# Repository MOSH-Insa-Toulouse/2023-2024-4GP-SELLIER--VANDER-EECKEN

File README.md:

<h1 align="center">📈 Projet capteur graphène 📉</h1>
<h2 align="center">👨‍🔬 Par VANDER-EECKEN Néo et SELLIÉ Pierre 👨‍🔬</h2>
<h3 align="center">🏫 Pour l'INSA de Toulouse, département du Génie Physique, année 2023 - 2024 🎓</h3>

<p align="center">
  
</p>

<h1 align="center">🔩 Mesure de contrainte avec capteur graphène sous Arduino 🤖</h1>

## 📝 Description

Ce projet introduit une approche novatrice pour la mesure de contrainte en exploitant les propriétés uniques du graphène à travers un capteur dédié, envisagé comme une alternative prometteuse aux jauges de contrainte conventionnelles. Grâce à l'emploi du graphène, connu pour sa sensibilité et sa flexibilité, ce capteur offre un potentiel intéressant pour une variété d'applications de mesure. Le système est bâti autour d'une plateforme Arduino, facilitant ainsi son accessibilité et sa manipulation pour tous.

Le projet inclut un circuit d'amplification pour le signal du capteur en graphène, assurant une précision accrue des mesures. Un potentiomètre digital permet d'ajuster le gain de ce circuit, offrant ainsi une calibration précise selon les besoins spécifiques de l'application. Cette approche est complétée par des modules tels que le Bluetooth, un écran OLED et un encodeur rotatoire, qui enrichissent l'expérience utilisateur et la fonctionnalité du système.

En complément de la programmation Arduino, ce projet est accompagné de fichiers KiCad détaillant le design d'un Shield UNO personnalisé. Cette approche modulaire facilite le montage et l'intégration de l'ensemble des composants, permettant ainsi une grande flexibilité dans la configuration du système.

## 🌟 Fonctionnalités

- **Capteur de contrainte en graphène** : Exploite les propriétés du graphène pour une mesure de contrainte.
- **Circuit d'amplification avec réglage** : Potentiomètre digital pour ajuster le gain.
- **Modules intégrés** : Communication Bluetooth, affichage sur écran OLED et interaction utilisateur via encodeur rotatoire.
- **Design modulaire** : Fichiers KiCad pour un Shield UNO personnalisé.

Pour plus d'informations, vous pouvez retrouver la datasheet du produit [ici](https://github.com/MOSH-Insa-Toulouse/2023-2024-4GP-SELLIER--VANDER-EECKEN/blob/main/Datasheet.pdf).

## 📦 Matériel nécessaire

- Capteur graphène (à fabriquer soi-même)
- Arduino UNO (https://store.arduino.cc/products/arduino-uno-rev3)
- Circuit d'amplification : LTC1050#CN8 + 2x100kΩ ; 10kΩ ; 1kΩ ; 3x100nF ; 1µF (https://www.analog.com/en/products/ltc1050.html)
- Potentiomètre digital : MCP41050-IP (https://www.microchip.com/en-us/product/mcp41050)
- Module Bluetooth : HC-05 (https://www.gotronic.fr/art-module-bluetooth-hc05-26097.htm)
- Écran OLED : SSD1306 (https://electropeak.com/0-96-oled-64x128-display-module)
- Encodeur rotatoire (https://www.az-delivery.de/fr/products/drehimpulsgeber-modul)
- Capteur FLEX (https://www.kiwi-electronics.com/en/short-flex-bend-sensor-2172)

## 🔧 Installation

1. Assemblez le circuit selon les schémas fournis dans les fichiers KiCad.
2. Connectez les modules et le capteur en suivant le schéma KiCad.
3. Installez l'IDE Arduino et installez la librairie "U8glib"
4. Téléchargez le code source sur votre Arduino UNO.

## 🖥️ Utilisation

Utilisez l'encodeur rotatoire pour naviguer dans le menu de l'écran OLED.

## 🤝 Contribuer

Les contributions sont bienvenues ! Si vous avez des idées d'amélioration, n'hésitez pas à forker le projet, soumettre des pull requests ou ouvrir des issues.

## 📜 Licence

Distribué sous la GNU General Public License (GPL), favorisant un écosystème ouvert et collaboratif.

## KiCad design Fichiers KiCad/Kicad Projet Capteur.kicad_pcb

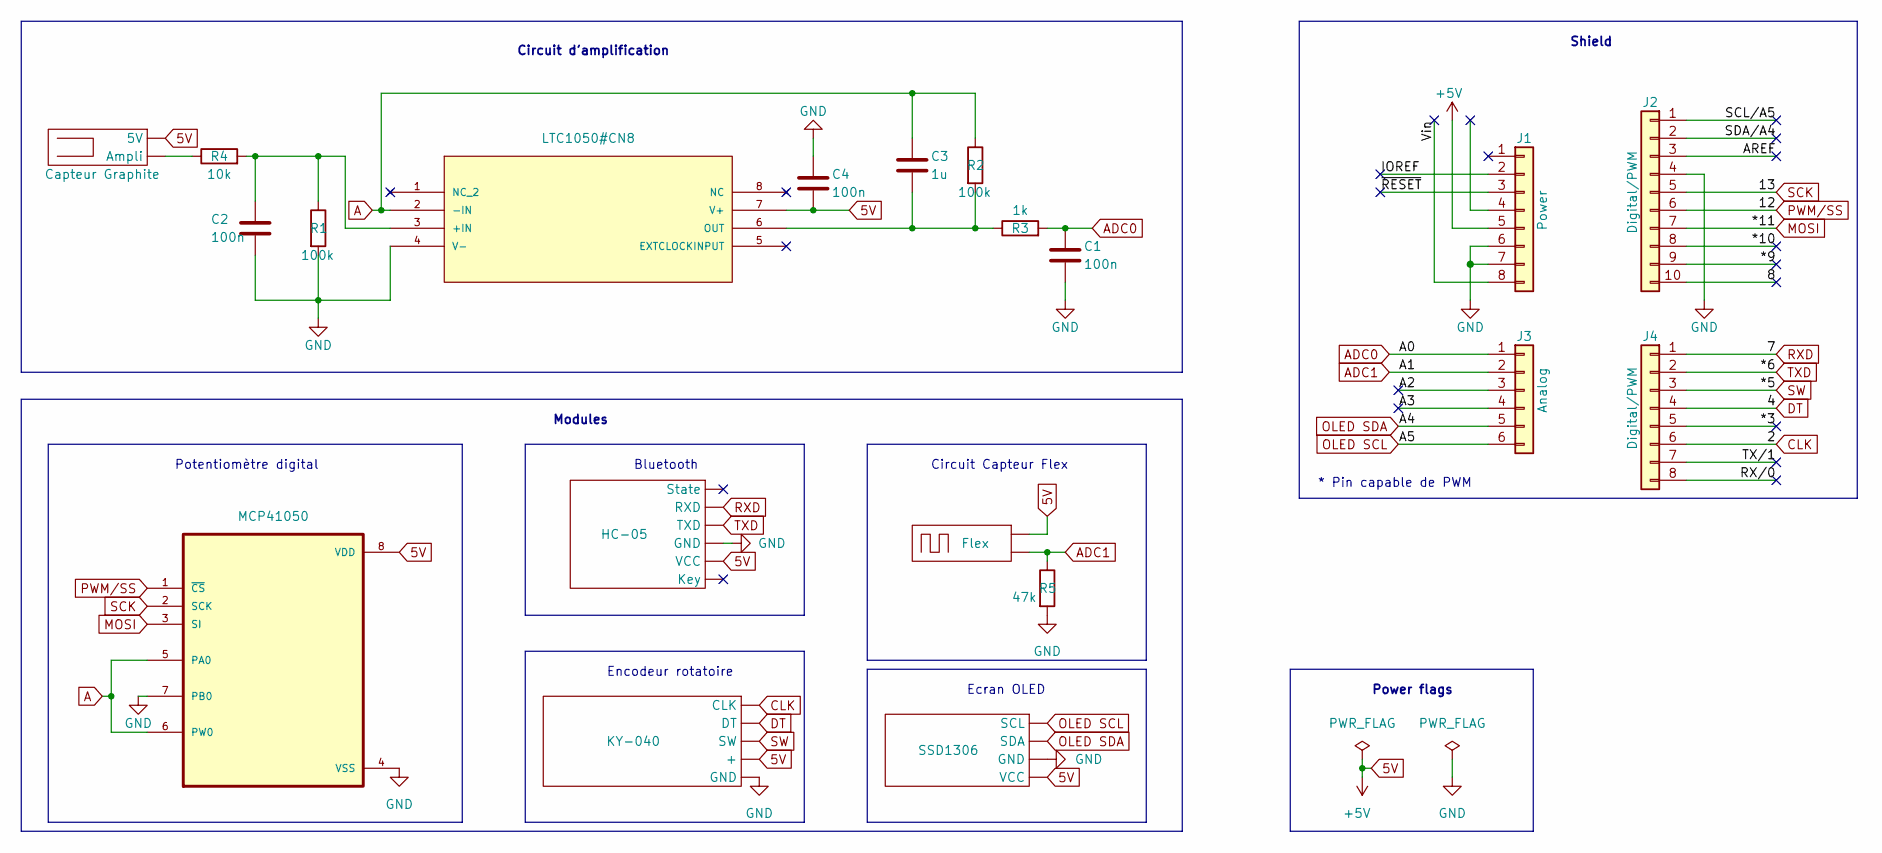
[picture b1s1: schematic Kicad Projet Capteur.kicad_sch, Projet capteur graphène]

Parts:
C1, C2, C4: 100n; C_Disc_D4.3mm_W1.9mm_P5.00mm
C3: 1u; C_Rect_L7.0mm_W4.5mm_P5.00mm
Capteur-Graphite1: Capteur Graphite; PinSocket_1x02_P2.54mm_Vertical
Flex1: Flex; PinSocket_1x02_P2.54mm_Vertical
HC-5: HC-05; PinSocket_1x06_P2.54mm_Vertical
J1: Power; PinSocket_1x08_P2.54mm_Vertical
J2: Digital/PWM; PinSocket_1x10_P2.54mm_Vertical
J3: Analog; PinSocket_1x06_P2.54mm_Vertical
J4: Digital/PWM; PinSocket_1x08_P2.54mm_Vertical
Pot1: KY-040; PinSocket_1x05_P2.54mm_Vertical
R1, R2: 100k; R_Axial_DIN0204_L3.6mm_D1.6mm_P5.08mm_Horizontal
R3: 1k; R_Axial_DIN0204_L3.6mm_D1.6mm_P5.08mm_Horizontal
R4: 10k; R_Axial_DIN0204_L3.6mm_D1.6mm_P5.08mm_Horizontal
R5: 47k; R_Axial_DIN0204_L3.6mm_D1.6mm_P5.08mm_Horizontal
SSD1306: SSD1306; PinSocket_1x04_P2.54mm_Vertical
U1: LTC1050#CN8; LTC1050; MANUFACTURER_PART_NUMBER ltc1050cn8
U2: MCP41050; MCP

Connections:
5V: C4.2, Capteur-Graphite1.1 (5V), Flex1.1 (+), HC-5.5 (VCC), J1.5, Pot1.4 (+), SSD1306.4 (VCC), U1.7 (V+), U2.8 (VDD)
/8: J2.10
/*3: J4.5
/*9: J2.9
/*10: J2.8
/A2: J3.3
/A3: J3.4
/AREF: J2.3
/IOREF: J1.2
/RX/0: J4.8
/SCL/A5: J2.1
/SDA/A4: J2.2
/TX/1: J4.7
/Vin: J1.8
/~RESET: J1.3
A: C3.1, R2.1, U1.2 (-IN), U2.5 (PA0), U2.6 (PW0)
ADC0: C1.1, J3.1, R3.2
ADC1: Flex1.2 (-), J3.2, R5.1
CLK: J4.6, Pot1.1 (CLK)
DT: J4.4, Pot1.2 (DT)
GND: C1.2, C2.2, C4.1, HC-5.4 (GND), J1.6, J1.7, J2.4, Pot1.5 (GND), R1.2, R5.2, SSD1306.3 (GND), U1.4 (V-), U2.4 (VSS), U2.7 (PB0)
MOSI: J2.7, U2.3 (SI)
unnamed: Capteur-Graphite1.2 (Ampli), R4.1
unnamed: C2.1, R1.1, R4.2, U1.3 (+IN)
unnamed: C3.2, R2.2, R3.1, U1.6 (OUT)
OLED SCL: J3.6, SSD1306.1 (SCL)
OLED SDA: J3.5, SSD1306.2 (SDA)
PWM/SS: J2.6, U2.1 (~CS)
RXD: HC-5.2 (RXD), J4.1
SCK: J2.5, U2.2 (SCK)
SW: J4.3, Pot1.3 (SW)
TXD: HC-5.3 (TXD), J4.2

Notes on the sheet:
Potentiomètre digital
Circuit d'amplification
Power flags
Bluetooth
Ecran OLED
Circuit Capteur Flex
* Pin capable de PWM
Modules
Shield
Encodeur rotatoire

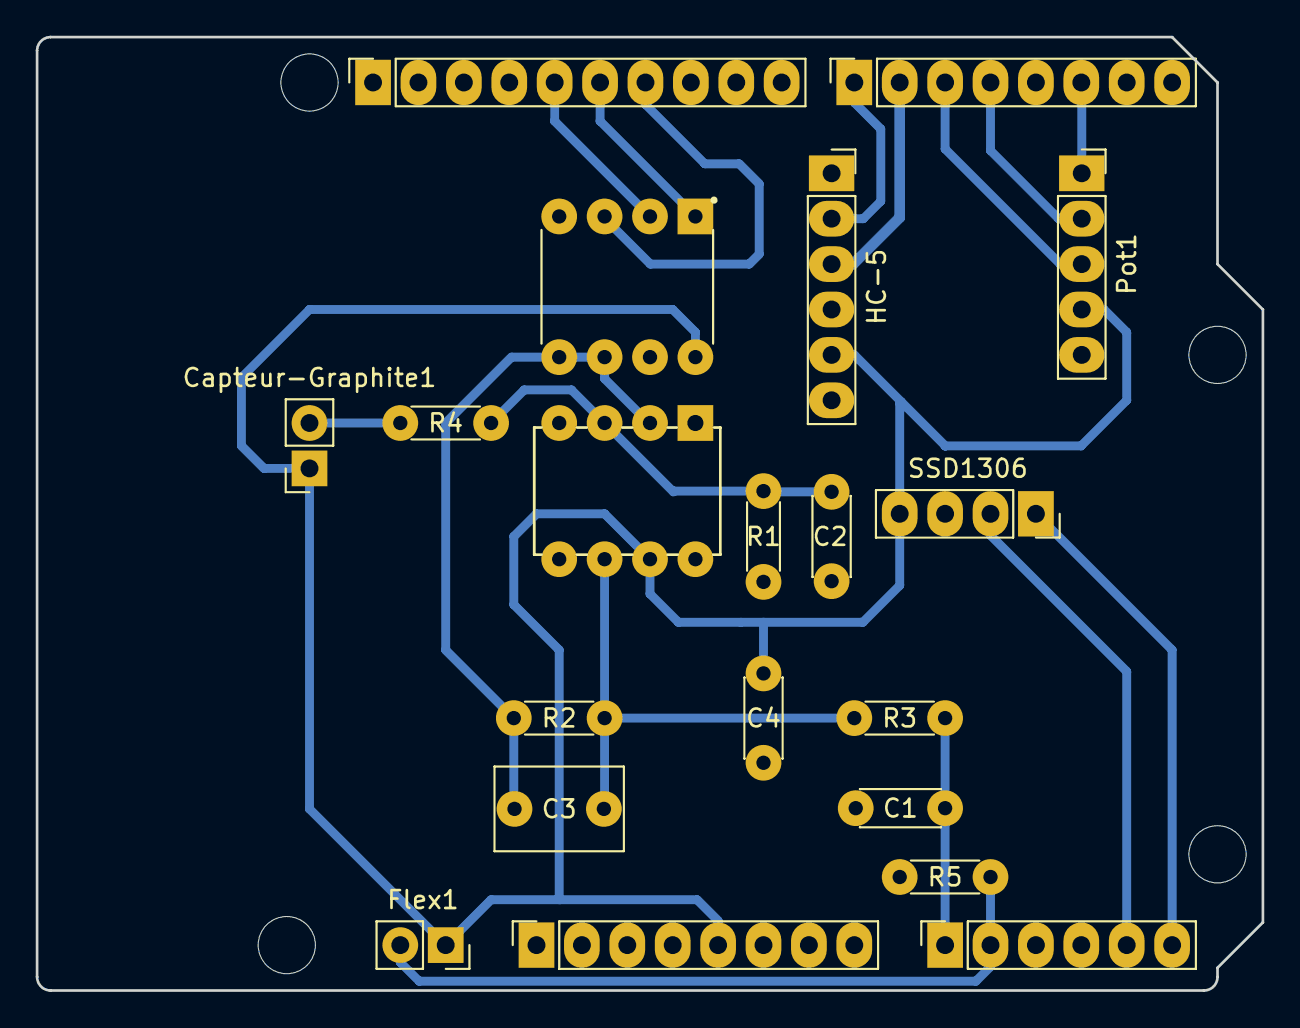
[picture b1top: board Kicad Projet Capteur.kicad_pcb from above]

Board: 2 copper layers, 68.6 x 53.3 mm, 24 parts (0 on the bottom side), 18 nets.

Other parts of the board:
MH1, MH2, MH3, MH4: MountingHole_3.2mm

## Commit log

2024-03-08 Bon format de readme
2024-03-08 Nouveau README.md
    Ajout d'émojis pour rendre le readme plus vivant.
    Changement du titre, des auteurs et du contexte
    Ajout du centrage des textes
2024-03-08 GIF de présentation du PCB
2024-03-08 Nouveau README.md
    GIF de présentation
2024-03-08 Ajout des fichiers KiCad
2024-03-08 Nouveau README.md
    Ajout des liens
    Quelques changements de texte
2024-03-08 Nouveau README.md
    Changement du titre
2024-03-08 Nouveau README.md
    Ajout du capteur FLEX
2024-03-08 Amélioration du GIF
    Boucle parfaite
2024-03-08 Gif pour la présentation du PCB
    Boucle parfaite
2024-03-08 Nouveau README.md
    Meilleurs instructions d'installation
2024-03-08 Ajout des fichiers Arduino
    1ère version avec juste les initialisations
2024-03-11 Amélioration layout KiCad
    OLED +
2024-03-11 Nouveau PCB + Nouveau GIF
    Plan de masse un peu plus propre et mise à jour du GIF
2024-03-13 Code du MCP41050 + Gain dynamique
2024-03-13 Create Capteur.aia
    Fichier application
2024-03-13 Update Capteur.aia
    Changement nom de variables
2024-03-14 fonctions bluetooth arduino + appli
    Création fonctions bluetooth arduino + ajout graphe flex sensor pour l'appplication
2024-03-14 Ajout du flex et de l'encodeur + bluetooth corrigé
2024-03-14 Ajout capteur + OLED avec menus + switch
2024-03-14 Nouveau README.md
    Correction des librairies utilisées
2024-03-16 Fix bluetooth + animations
2024-03-18 Fix du MCP41050
    - Mappage corrigé
    - Passage en double
    - Gestion plus simple du SPI
2024-05-12 Added datasheet, fixed ground plane

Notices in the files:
README.md:
License: GPL v3
